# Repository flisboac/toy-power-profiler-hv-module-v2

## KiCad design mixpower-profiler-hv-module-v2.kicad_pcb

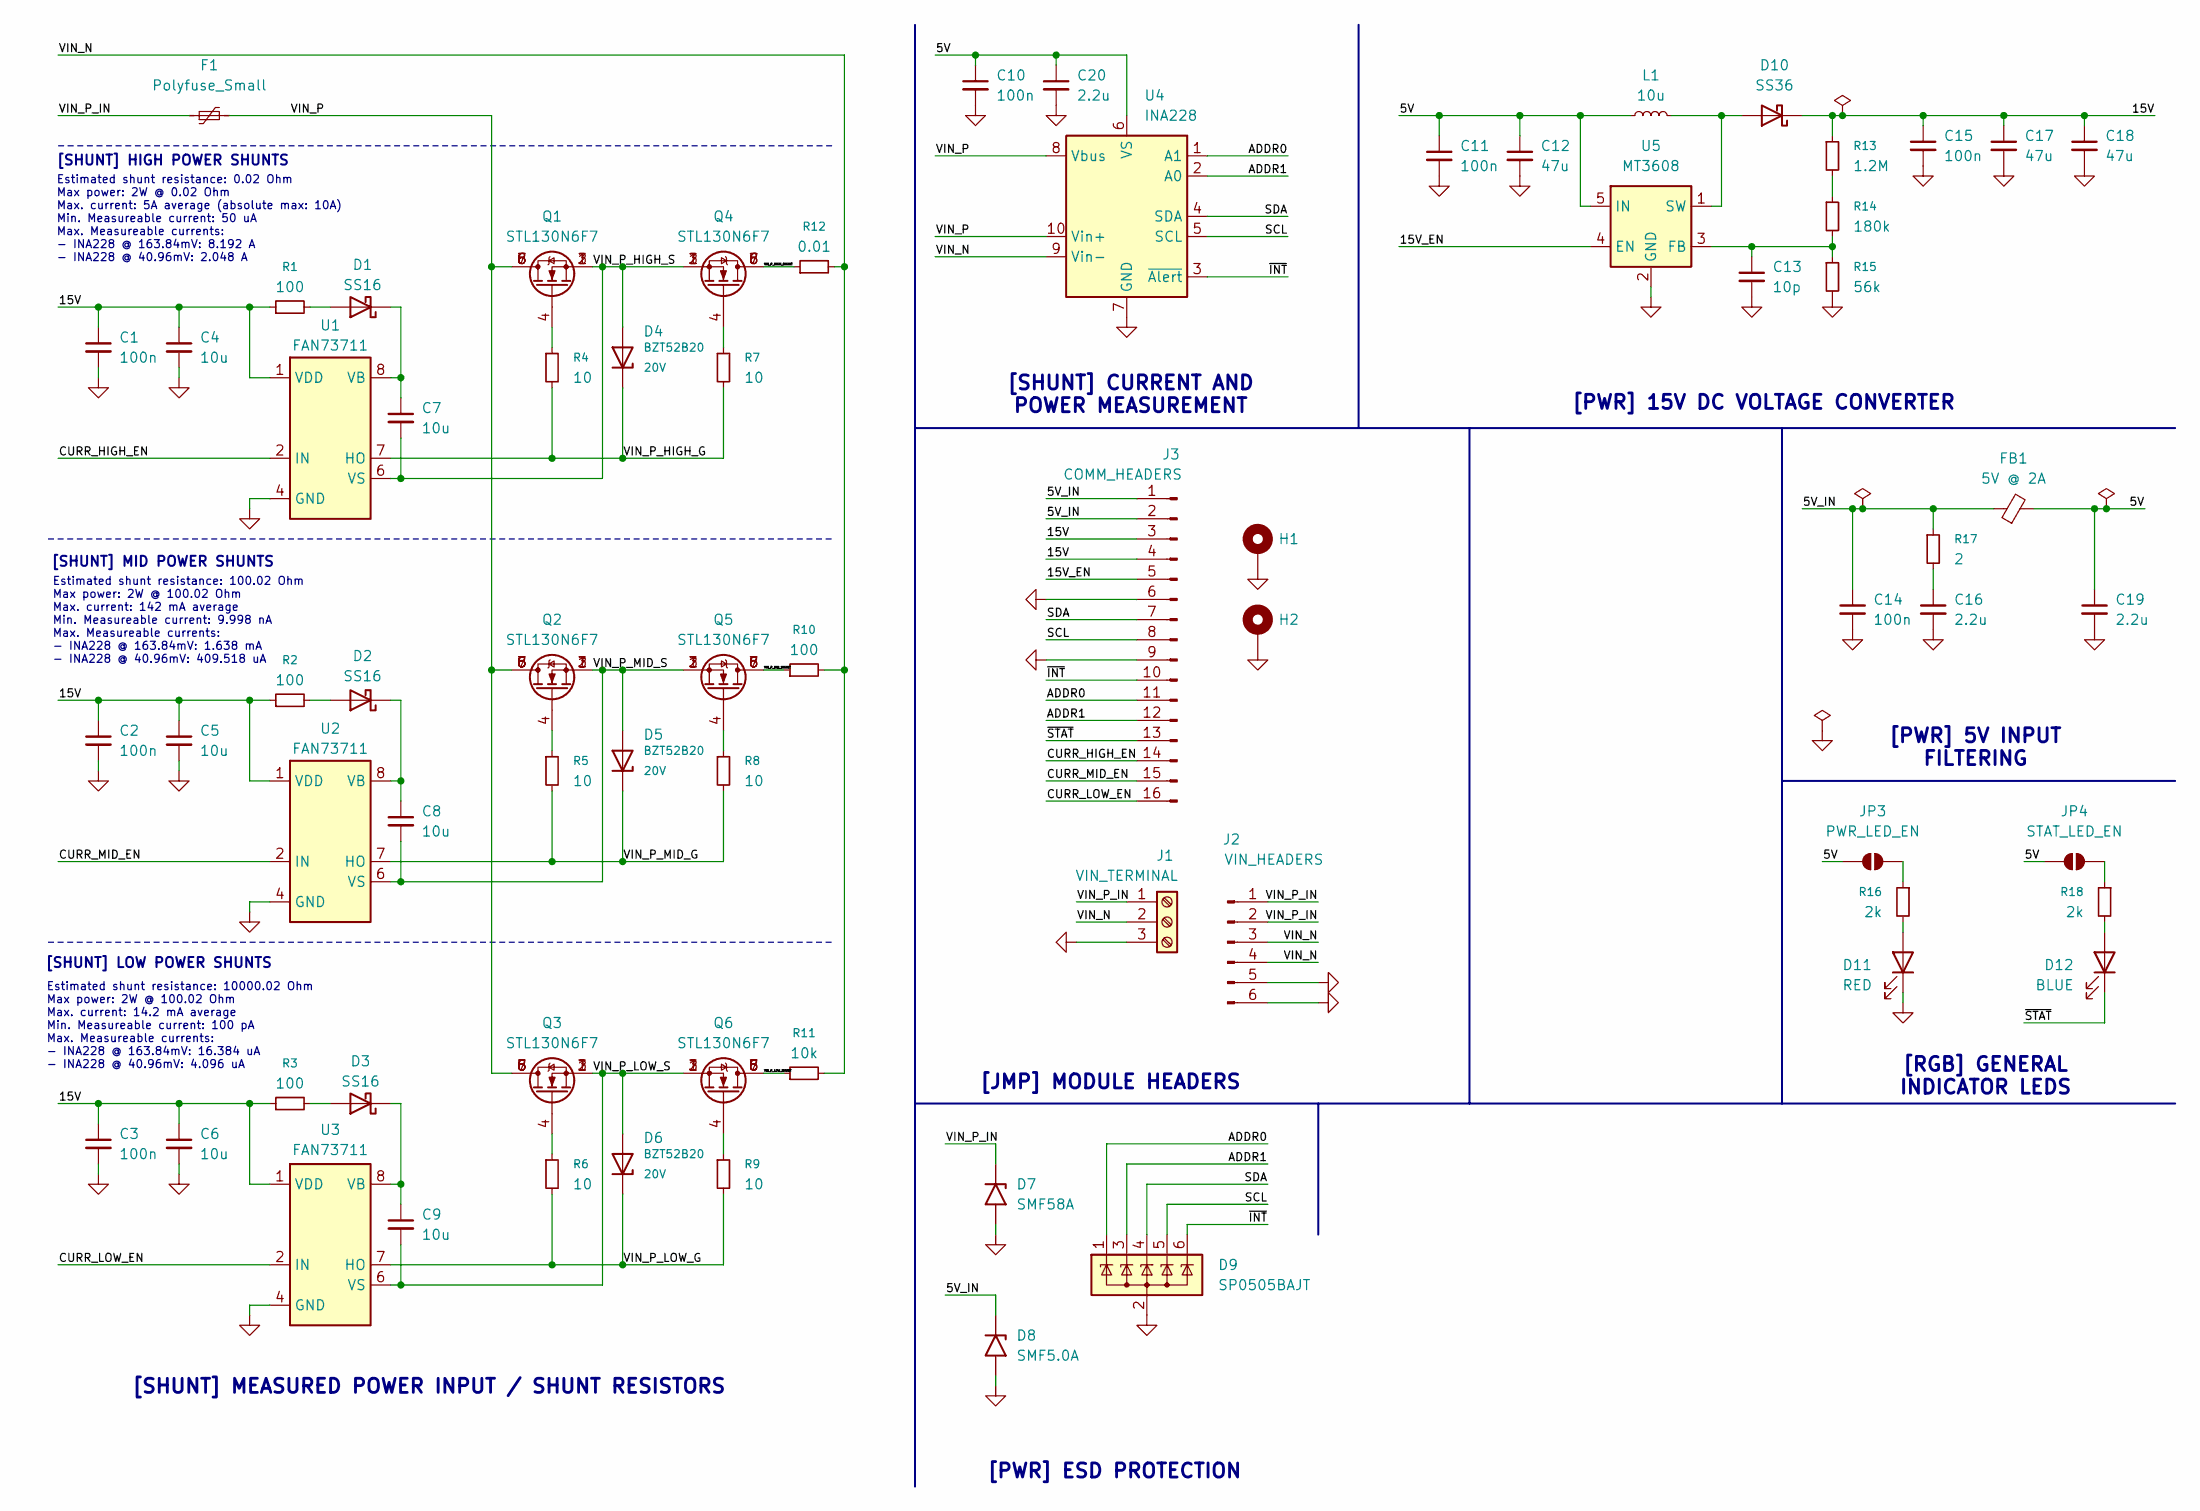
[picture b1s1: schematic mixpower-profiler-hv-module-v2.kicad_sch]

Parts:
C1, C2, C3, C10, C11, C14, C15: 100n; C_0402_1005Metric
C4, C5, C6, C7, C8, C9: 10u; C_0805_2012Metric
C12, C17, C18: 47u; C_0805_2012Metric
C13: 10p; C_0402_1005Metric
C16, C19, C20: 2.2u; C_0805_2012Metric
D1, D2, D3: SS16; D_SMA
D4, D5, D6: BZT52B20; D_SOD-123F; Voltage 20V
D7: SMF58A; D_SMF
D8: SMF5.0A; D_SMF
D9: SP0505BAJT; SOT-363_SC-70-6
D10: SS36; D_SMA
D11: RED; LED_0603_1608Metric
D12: BLUE; LED_0603_1608Metric
F1: Polyfuse_Small; R_1812_4532Metric
FB1: 5V @ 2A; L_1206_3216Metric
H1: MountingHole_Pad; MountingHole_2.2mm_M2_ISO7380_Pad_TopBottom
H2: MountingHole_Pad; MountingHole_2.2mm_M2_ISO14580_Pad_TopBottom
J1: VIN_TERMINAL; TerminalBlock_bornier-3_P5.08mm
J2: VIN_HEADERS; PinHeader_1x06_P2.54mm_Vertical
J3: COMM_HEADERS; PinHeader_1x16_P2.54mm_Vertical
JP3: PWR_LED_EN; SolderJumper-2_P1.3mm_Open_Pad1.0x1.5mm
JP4: STAT_LED_EN; SolderJumper-2_P1.3mm_Open_Pad1.0x1.5mm
L1: 10u; L_Changjiang_FXL0630
Q1, Q2, Q3, Q4, Q5, Q6: STL130N6F7; POWERFLAT_5X6_C_STM
R1, R2, R3: 100; R_0603_1608Metric
R4, R5, R6, R7, R8, R9: 10; R_0603_1608Metric
R10: 100; R_2512_6332Metric
R11: 10k; R_2512_6332Metric
R12: 0.01; R_2512_6332Metric
R13: 1.2M; R_0402_1005Metric
R14: 180k; R_0402_1005Metric
R15: 56k; R_0402_1005Metric
R16, R18: 2k; R_0402_1005Metric
R17: 2; R_0805_2012Metric
U1, U2, U3: FAN73711; SOIC-8_3.9x4.9mm_P1.27mm
U4: INA228; VSSOP-10_3x3mm_P0.5mm
U5: MT3608; SOT-23-6

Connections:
/5V: C10.1, C11.1, C12.1, C19.1, C20.1, FB1.2, JP3.1 (A), JP4.1 (A), L1.1, U4.6 (VS), U5.5 (IN)
/5V_IN: C14.1, D8.1 (A1), FB1.1, J3.1, J3.2, R17.1; also elsewhere on the board
/15V: C1.1, C2.1, C3.1, C4.1, C5.1, C6.1, C15.1, C17.1, C18.1, D10.1 (K), J3.3, J3.4, R1.1, R2.1, R3.1, R13.1, U1.1 (VDD), U2.1 (VDD), U3.1 (VDD); also elsewhere on the board
/15V_EN: J3.5, U5.4 (EN); also elsewhere on the board
/ADDR0: D9.1 (K), J3.11, U4.1 (A1); also elsewhere on the board
/ADDR1: D9.3 (K), J3.12, U4.2 (A0); also elsewhere on the board
/CURR_HIGH_EN: J3.14, U1.2 (IN); also elsewhere on the board
/CURR_LOW_EN: J3.16, U3.2 (IN); also elsewhere on the board
/CURR_MID_EN: J3.15, U2.2 (IN); also elsewhere on the board
/SCL: D9.5 (K), J3.8, U4.5 (SCL); also elsewhere on the board
/SDA: D9.4 (K), J3.7, U4.4 (SDA); also elsewhere on the board
/VIN_N: J1.2, J2.3, J2.4, R10.2, R11.2, R12.2, U4.9 (Vin-)
/VIN_P: F1.2, Q1.5 (D), Q1.6 (D), Q1.7 (D), Q1.8 (D), Q2.5 (D), Q2.6 (D), Q2.7 (D), Q2.8 (D), Q3.5 (D), Q3.6 (D), Q3.7 (D), Q3.8 (D), U4.8 (Vbus), U4.10 (Vin+)
/VIN_P_HIGH_G: D4.1 (K), R4.2, R7.2, U1.7 (HO)
/VIN_P_HIGH_S: C7.2, D4.2 (A), Q1.1 (S), Q1.2 (S), Q1.3 (S), Q4.1 (S), Q4.2 (S), Q4.3 (S), U1.6 (VS)
/VIN_P_HIGH_SHUNT: Q4.5 (D), Q4.6 (D), Q4.7 (D), Q4.8 (D), R12.1
/VIN_P_IN: D7.1 (A1), F1.1, J1.1, J2.1, J2.2
/VIN_P_LOW_G: D6.1 (K), R6.2, R9.2, U3.7 (HO)
/VIN_P_LOW_S: C9.2, D6.2 (A), Q3.1 (S), Q3.2 (S), Q3.3 (S), Q6.1 (S), Q6.2 (S), Q6.3 (S), U3.6 (VS)
/VIN_P_LOW_SHUNT: Q6.5 (D), Q6.6 (D), Q6.7 (D), Q6.8 (D), R11.1
/VIN_P_MID_G: D5.1 (K), R5.2, R8.2, U2.7 (HO)
/VIN_P_MID_S: C8.2, D5.2 (A), Q2.1 (S), Q2.2 (S), Q2.3 (S), Q5.1 (S), Q5.2 (S), Q5.3 (S), U2.6 (VS)
/VIN_P_MID_SHUNT: Q5.5 (D), Q5.6 (D), Q5.7 (D), Q5.8 (D), R10.1
/~INT: D9.6 (K), J3.10, U4.3 (~Alert); also elsewhere on the board
/~STAT: D12.1 (K), J3.13; also elsewhere on the board
GND: C1.2, C2.2, C3.2, C4.2, C5.2, C6.2, C10.2, C11.2, C12.2, C13.2, C14.2, C15.2, C16.2, C17.2, C18.2, C19.2, C20.2, D7.2 (A2), D8.2 (A2), D9.2 (A), D11.1 (K), H1.1, H2.1, J1.3, J2.5, J2.6, J3.6, J3.9, R15.2, U1.4 (GND), U2.4 (GND), U3.4 (GND), U4.7 (GND), U5.2 (GND); also elsewhere on the board
unnamed: C16.1, R17.2
unnamed: D1.2 (A), R1.2
unnamed: C7.1, D1.1 (K), U1.8 (VB)
unnamed: D2.2 (A), R2.2
unnamed: C8.1, D2.1 (K), U2.8 (VB)
unnamed: D3.2 (A), R3.2
unnamed: C9.1, D3.1 (K), U3.8 (VB)
unnamed: D10.2 (A), L1.2, U5.1 (SW)
unnamed: D11.2 (A), R16.2
unnamed: D12.2 (A), R18.2
unnamed: JP3.2 (B), R16.1
unnamed: JP4.2 (B), R18.1
unnamed: Q1.4 (G), R4.1
unnamed: Q2.4 (G), R5.1
unnamed: Q3.4 (G), R6.1
unnamed: Q4.4 (G), R7.1
unnamed: Q5.4 (G), R8.1
unnamed: Q6.4 (G), R9.1
unnamed: R13.2, R14.1
unnamed: C13.1, R14.2, R15.1, U5.3 (FB)

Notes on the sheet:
[SHUNT] LOW POWER SHUNTS
Estimated shunt resistance: 0.02 Ohm Max power: 2W @ 0.02 Ohm Max. current: 5A average (absolute max: 10A) Min. Measureable current: 50 uA Max. Measureable currents: - INA228 @ 163.84mV: 8.192 A - INA228 @ 40.96mV: 2.048 A
[PWR] 15V DC VOLTAGE CONVERTER
[SHUNT] CURRENT AND POWER MEASUREMENT
Estimated shunt resistance: 100.02 Ohm Max power: 2W @ 100.02 Ohm Max. current: 142 mA average Min. Measureable current: 9.998 nA Max. Measureable currents: - INA228 @ 163.84mV: 1.638 mA - INA228 @ 40.96mV: 409.518 uA
[SHUNT] MEASURED POWER INPUT / SHUNT RESISTORS
[JMP] MODULE HEADERS
[RGB] GENERAL INDICATOR LEDS
[PWR] 5V INPUT FILTERING
[SHUNT] MID POWER SHUNTS
[PWR] ESD PROTECTION
[SHUNT] HIGH POWER SHUNTS
Estimated shunt resistance: 10000.02 Ohm Max power: 2W @ 100.02 Ohm Max. current: 14.2 mA average Min. Measureable current: 100 pA Max. Measureable currents: - INA228 @ 163.84mV: 16.384 uA - INA228 @ 40.96mV: 4.096 uA

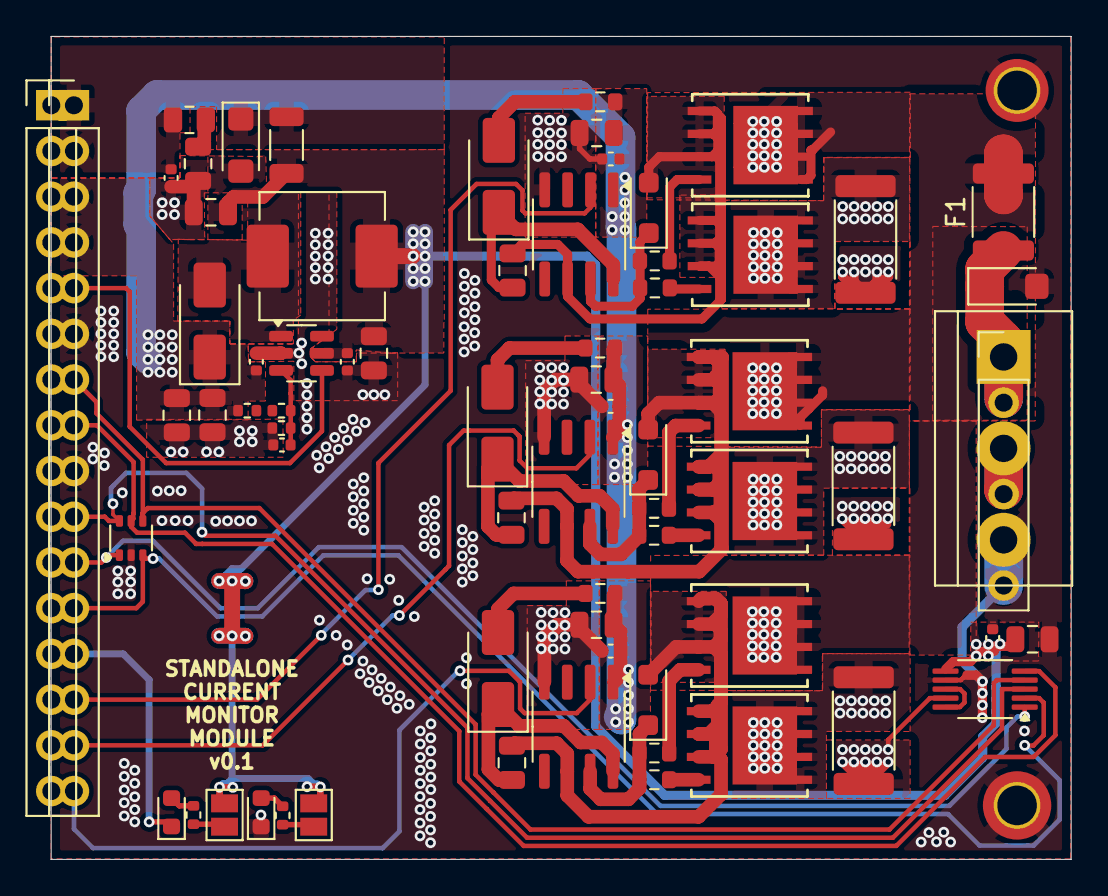
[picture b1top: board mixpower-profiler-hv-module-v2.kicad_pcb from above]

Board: 2 copper layers, 56.7 x 45.7 mm, 72 parts (0 on the bottom side), 46 nets.

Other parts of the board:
J3_CASTELLATIONS: COMM_HEADERS; PinHeader_1x16_P2.54mm_Vertical

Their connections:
/5V_IN: J3_CASTELLATIONS.1, J3_CASTELLATIONS.2; also elsewhere on the board
/15V: J3_CASTELLATIONS.3, J3_CASTELLATIONS.4; also elsewhere on the board
/15V_EN: J3_CASTELLATIONS.5; also elsewhere on the board
/ADDR0: J3_CASTELLATIONS.11; also elsewhere on the board
/ADDR1: J3_CASTELLATIONS.12; also elsewhere on the board
/CURR_HIGH_EN: J3_CASTELLATIONS.14; also elsewhere on the board
/CURR_LOW_EN: J3_CASTELLATIONS.16; also elsewhere on the board
/CURR_MID_EN: J3_CASTELLATIONS.15; also elsewhere on the board
/SCL: J3_CASTELLATIONS.8; also elsewhere on the board
/SDA: J3_CASTELLATIONS.7; also elsewhere on the board
/~INT: J3_CASTELLATIONS.10; also elsewhere on the board
/~STAT: J3_CASTELLATIONS.13; also elsewhere on the board
GND: J3_CASTELLATIONS.6, J3_CASTELLATIONS.9; also elsewhere on the board

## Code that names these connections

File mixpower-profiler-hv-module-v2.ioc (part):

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Mcu.Name=STM32C071GBUxN
Mcu.Package=UFQFPN28_N
Mcu.UserName=STM32C071GBUxN
PA0.Mode=Full_Duplex_Master
PA0.Signal=SPI2_SCK
PA1.Mode=Full_Duplex_Master
PA1.Signal=SPI1_SCK
PA11\ [PA9].Mode=Device
PA11\ [PA9].Signal=USB_DM
PA12\ [PA10].Mode=Device
PA12\ [PA10].Signal=USB_DP
PA13.Mode=Serial_Wire
PA13.Signal=DEBUG_SWDIO
PA14-BOOT0.Mode=Serial_Wire
PA14-BOOT0.Signal=DEBUG_SWCLK
PA15.GPIOParameters=GPIO_Label
PA15.GPIO_Label=GPIO\:ADDR0
PA15.Signal=GPIO_Output
PA2.Mode=Half_duplex(single_wire_mode)
PA2.Signal=USART2_TX
PA3.Mode=Full_Duplex_Master
PA3.Signal=SPI2_MISO
PA4.Mode=Full_Duplex_Master
PA4.Signal=SPI2_MOSI
PA5.GPIOParameters=GPIO_Label
PA5.GPIO_Label=GPIO\:STAT
PA5.Signal=GPIO_Output
PA6.Mode=Full_Duplex_Master
PA6.Signal=SPI1_MISO
PA7.Mode=Full_Duplex_Master
PA7.Signal=SPI1_MOSI
PA8.GPIOParameters=GPIO_Label
PA8.GPIO_Label=GPIO\:CURR_LOW_EN
PA8.Signal=GPIO_Output
PB0.GPIOParameters=GPIO_Label
PB0.GPIO_Label=GPIO\:CURR_HIGH_EN
PB0.Signal=GPIO_Output
PB1.GPIOParameters=GPIO_Label
PB1.GPIO_Label=GPIO\:CURR_MID_EN
PB1.Signal=GPIO_Output
PB3.Mode=I2C
PB3.Signal=I2C2_SCL
PB4.Mode=I2C
PB4.Signal=I2C2_SDA
PB5.Signal=GPXTI5
PB6.Mode=I2C
PB6.Signal=I2C1_SCL
PB7.Mode=I2C
PB7.Signal=I2C1_SDA
PB8.GPIOParameters=GPIO_Label
PB8.GPIO_Label=GPIO\:ADDR1
PB8.Signal=GPIO_Output
PC14-OSCX_IN(PC14).Mode=HSE-External-Oscillator
PC14-OSCX_IN(PC14).Signal=RCC_OSCX_IN
PC15-OSCX_OUT(PC15).Mode=HSE-External-Oscillator
PC15-OSCX_OUT(PC15).Signal=RCC_OSCX_OUT
RCC.HSE_VALUE=48000000
RCC.SYSCLKFreq_VALUE=48000000
RCC.SYSCLKSource=RCC_SYSCLKSOURCE_HSIUSB48
board=custom

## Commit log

2025-05-06 feat: initial commit
2025-05-06 feat: add rendered board and schematics
2025-05-06 feat: add PTC fuse on VIN
